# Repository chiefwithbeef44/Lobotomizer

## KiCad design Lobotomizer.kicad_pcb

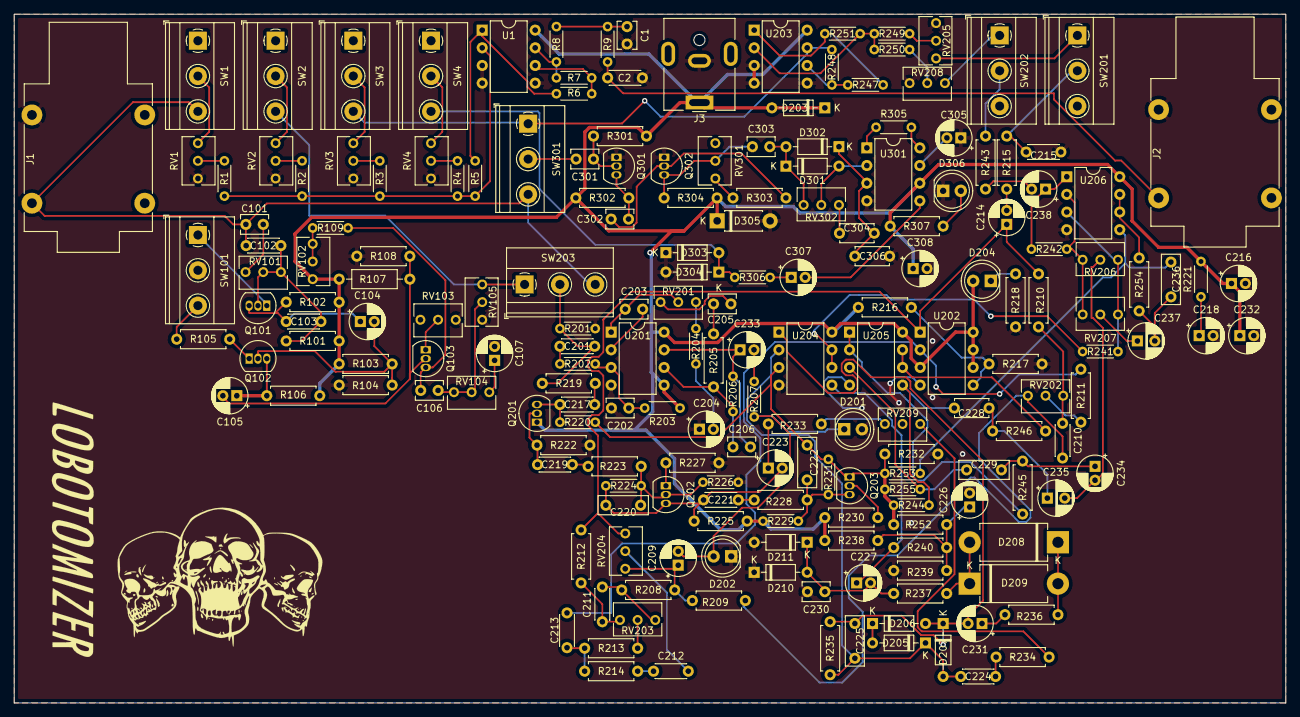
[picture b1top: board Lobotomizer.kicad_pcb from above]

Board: 2 copper layers, 182.9 x 99.1 mm, 198 parts (0 on the bottom side), 128 nets.

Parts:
C1, C202, C230: 1n; C_Disc_D3.8mm_W2.6mm_P2.50mm
C2: 680p; C_Disc_D4.3mm_W1.9mm_P5.00mm
C101, C106, C205, C301, C302, C303: 100n; C_Disc_D3.8mm_W2.6mm_P2.50mm
C102, C211, C213: 10n; C_Disc_D4.3mm_W1.9mm_P5.00mm
C103: 470p; C_Disc_D4.3mm_W1.9mm_P5.00mm
C104, C105, C305: 4.7u; CP_Radial_D5.0mm_P2.00mm
C107: 330n; CP_Radial_D5.0mm_P2.00mm
C201, C215: 22n; C_Disc_D4.3mm_W1.9mm_P5.00mm
C203, C206: 100p; C_Disc_D3.8mm_W2.6mm_P2.50mm
C204: 220n; CP_Radial_D5.0mm_P2.00mm
C209, C214, C233: 2.2u; CP_Radial_D5.0mm_P2.00mm
C210, C217, C219, C221, C224: 47n; C_Disc_D4.3mm_W1.9mm_P5.00mm
C212: 2.2n; C_Disc_D4.3mm_W1.9mm_P5.00mm
C216, C232, C307, C308: 100u; CP_Radial_D5.0mm_P2.00mm
C218, C226: 47u; CP_Radial_D5.0mm_P2.00mm
C220, C222, C225: 10p; C_Disc_D7.0mm_W2.5mm_P5.00mm
C223, C238: 10u; CP_Radial_D5.0mm_P2.00mm
C227, C231: 1u; CP_Radial_D5.0mm_P2.00mm
C228, C304: 6.8n; C_Disc_D4.7mm_W2.5mm_P5.00mm
C229: 4.7n; C_Disc_D7.0mm_W2.5mm_P5.00mm
C234: 0.1u; CP_Radial_D5.0mm_P2.00mm
C235: 0.15u; CP_Radial_D5.0mm_P2.50mm
C236: 68n; C_Disc_D7.0mm_W2.5mm_P5.00mm
C237: 1.5u; CP_Radial_D5.0mm_P2.50mm
C306: 220p; C_Disc_D4.7mm_W2.5mm_P5.00mm
D201, D202, D204, D306: LED; LED_D5.0mm
D203, D205, D206, D207, D210, D211: 4148; D_DO-35_SOD27_P7.62mm_Horizontal
D208, D209: SB2060; D_DO-201AD_P12.70mm_Horizontal
D301, D302, D303, D304: 5227; D_DO-35_SOD27_P7.62mm_Horizontal
D305: 4001; D_DO-41_SOD81_P7.62mm_Horizontal
J1: IN; Jack_6.35mm_Neutrik_NMJ4HFD2_Horizontal
J2: OUT; Jack_6.35mm_Neutrik_NMJ4HFD2_Horizontal
J3: POWER; BarrelJack_CUI_PJ-063AH_Horizontal
Q101, Q102: 5089; TO-92_Inline
Q103: 5308; TO-92_Inline
Q201: NTE457; TO-92_Inline
Q202: 2N3904; TO-92_Inline
Q203: KSA992; TO-92_Inline
Q301, Q302: MPSA05; TO-92_Inline
R1, R2, R3, R4, R5, R6, R7, R8, R9, R226, R229, R244, R247, R248, R249, R250, R251, R253, R255: 100K; R_Axial_DIN0204_L3.6mm_D1.6mm_P5.08mm_Horizontal
R101, R103, R108, R301: 910K; R_Axial_DIN0207_L6.3mm_D2.5mm_P7.62mm_Horizontal
R102, R106, R302, R304: 180K; R_Axial_DIN0207_L6.3mm_D2.5mm_P7.62mm_Horizontal
R104: 910; R_Axial_DIN0207_L6.3mm_D2.5mm_P7.62mm_Horizontal
R105, R205, R214, R219, R222, R225, R232, R236, R237, R238, R239, R243, R307: 10K; R_Axial_DIN0207_L6.3mm_D2.5mm_P7.62mm_Horizontal
R107: 4.7M; R_Axial_DIN0207_L6.3mm_D2.5mm_P10.16mm_Horizontal
R109: 750; R_Axial_DIN0204_L3.6mm_D1.6mm_P5.08mm_Horizontal
R201, R203, R206, R220: 1M; R_Axial_DIN0204_L3.6mm_D1.6mm_P5.08mm_Horizontal
R202, R204, R221, R305: 1K; R_Axial_DIN0204_L3.6mm_D1.6mm_P5.08mm_Horizontal
R207: 470; R_Axial_DIN0204_L3.6mm_D1.6mm_P5.08mm_Horizontal
R208, R212: 2.2K; R_Axial_DIN0207_L6.3mm_D2.5mm_P7.62mm_Horizontal
R209, R210, R215: 6.8K; R_Axial_DIN0207_L6.3mm_D2.5mm_P7.62mm_Horizontal
R211, R240, R252: 68K; R_Axial_DIN0207_L6.3mm_D2.5mm_P7.62mm_Horizontal
R213: 15K; R_Axial_DIN0207_L6.3mm_D2.5mm_P7.62mm_Horizontal
R216, R217, R223, R228: 22K; R_Axial_DIN0207_L6.3mm_D2.5mm_P7.62mm_Horizontal
R218, R303: 4.7K; R_Axial_DIN0207_L6.3mm_D2.5mm_P7.62mm_Horizontal
R224, R231: 470K; R_Axial_DIN0204_L3.6mm_D1.6mm_P5.08mm_Horizontal
R227: 22; R_Axial_DIN0207_L6.3mm_D2.5mm_P7.62mm_Horizontal
R230: 120; R_Axial_DIN0207_L6.3mm_D2.5mm_P7.62mm_Horizontal
R233: 150; R_Axial_DIN0207_L6.3mm_D2.5mm_P7.62mm_Horizontal
R234: 47K; R_Axial_DIN0207_L6.3mm_D2.5mm_P7.62mm_Horizontal
R235: 220K; R_Axial_DIN0207_L6.3mm_D2.5mm_P7.62mm_Horizontal
R241, R242: 3.3K; R_Axial_DIN0204_L3.6mm_D1.6mm_P5.08mm_Horizontal
R245, R246, R254: 330; R_Axial_DIN0207_L6.3mm_D2.5mm_P7.62mm_Horizontal
R306: 220; R_Axial_DIN0204_L3.6mm_D1.6mm_P5.08mm_Horizontal
RV1, RV2, RV3, RV4, RV101, RV105, RV201, RV204, RV205: 100K; Potentiometer_Bourns_3266Y_Vertical
RV102: 50K; Potentiometer_Bourns_3266Y_Vertical
RV103, RV104, RV206, RV207, RV208: 10K; Potentiometer_Bourns_3266Y_Vertical
RV202, RV203: 25K; Potentiometer_Bourns_3266Y_Vertical
RV209: 250K; Potentiometer_Bourns_3266Y_Vertical
RV301, RV302: 1M; Potentiometer_Bourns_3266Y_Vertical
SW1, SW2, SW3, SW4, SW201, SW202, SW203, SW301: SW_SPDT; TerminalBlock_Phoenix_MKDS-1,5-3-5.08_1x03_P5.08mm_Horizont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
SW101: SW_SPDT_MSM; TerminalBlock_Phoenix_MKDS-1,5-3-5.08_1x03_P5.08mm_Horizont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
U1, U202, U203: TL082; DIP-8_W7.62mm
U201, U204, U205, U206: LM833; DIP-8_W7.62mm
U301: LM386; DIP-8_W7.62mm

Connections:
4.5V: C222.1, Q203.1, R220.1, R231.1, R232.1, R244.2, R252.2, R253.2, R255.2, U204.3
FUZZ_OUT: RV105.3, SW2.3, SW203.1
GND: C1.2, C2.2, C107.2, C202.2, C204.1, C215.2, C216.2, C218.2, C226.2, C230.2, C232.2, C305.1, C306.2, C308.2, D201.2, D202.1, D210.1, D211.2, D303.1, D304.2, D305.2, D306.1, J1.S, J2.S, J3.2, Q301.1, Q302.1, R104.2, R108.2, R201.2, R217.2, R218.1, R222.2, R226.2, R227.2, R232.2, R239.2, RV1.3, RV2.3, RV3.3, RV4.3, RV103.1, RV105.1, RV205.3, RV208.3, RV209.2, SW101.2, U1.3, U1.4, U1.5, U201.4, U202.4, U203.3, U203.4, U203.5, U204.4, U205.4, U206.4, U301.4
MEGAFUCKER_OUT: R248.1, SW3.3, SW301.1, U203.7
unnamed: C1.1, R8.1, R9.2
unnamed: C2.1, J2.T, R9.1
unnamed: C101.1, RV101.3
unnamed: C102.1, C103.2, Q101.2, R101.2, RV101.1, RV101.2
unnamed: C103.1, C104.1, Q101.3, R102.2
unnamed: C104.2, Q102.2, R103.2, R104.1
unnamed: C105.1, Q102.3, R106.2
unnamed: C105.2, Q103.2, R107.2, R108.1
unnamed: C106.1, RV104.2, RV104.3, RV105.2
unnamed: C106.2, Q103.3, R109.2
unnamed: C107.1, RV104.1
unnamed: C201.1, R202.2
unnamed: C201.2, R201.1, R219.2, SW203.2
unnamed: C202.1, R202.1, R203.2, U201.3
unnamed: C203.1, RV201.2, U201.1
unnamed: C203.2, U201.2
unnamed: C204.2, R204.2
unnamed: C205.1, R205.2
unnamed: C205.2, RV201.3
unnamed: C206.1, R205.1, R206.1, U201.6
unnamed: C206.2, C233.1, R206.2, U201.7
unnamed: C209.1, R208.2, R209.2, RV204.3
unnamed: C209.2, D201.1, D202.2, R207.1
unnamed: C210.1, R210.2, RV202.1
unnamed: C210.2, R209.1, RV202.3
unnamed: C211.1, R212.2, RV203.1
unnamed: C211.2, R208.1, RV203.3
unnamed: C212.1, R214.2
unnamed: C212.2, RV204.2
unnamed: C213.1, R211.1, U202.2
unnamed: C213.2, R213.1, R214.1
unnamed: C214.1, R210.1, R212.1, RV204.1, U202.1
unnamed: C214.2, R215.2
unnamed: C215.1, R215.1, SW201.2
unnamed: C217.1, Q201.3, R220.2
unnamed: C217.2, R219.1
unnamed: C218.1, R221.1
unnamed: C219.1, R223.2
unnamed: C219.2, Q201.2, R222.1
unnamed: C220.1, C221.2, C223.2, Q202.3, R224.1, R225.2
unnamed: C220.2, Q202.2, R223.1, R224.2, R226.1
unnamed: C221.1, R228.2
unnamed: C222.2, Q203.3, R228.1, R229.2, R231.2
unnamed: C223.1, R233.2
unnamed: C224.1, C225.2, D205.1, D207.2, R235.2, U204.2
unnamed: C224.2, R234.1
unnamed: C225.1, C231.2, D206.2, D207.1, R235.1, U204.1
unnamed: C226.1, R238.2, R239.1, R240.1, R252.1
unnamed: C227.1, R240.2, U204.5
unnamed: C227.2, C230.1, D210.2, D211.1, R237.1
unnamed: C228.1, C235.1, R246.1
unnamed: C228.2, R244.1, U205.5
unnamed: C229.1, C234.1, R245.1
unnamed: C229.2, R255.1, U205.3
unnamed: C231.1, R236.2
unnamed: C233.2, R207.2
unnamed: C234.2, C235.2, RV206.2
unnamed: C236.1, C237.2, R254.1
unnamed: C236.2, R253.1, U206.5
unnamed: C237.1, RV207.2
unnamed: C238.1, R242.1, U206.1
unnamed: C238.2, R243.2
unnamed: C301.1, Q301.2, R301.2
unnamed: C301.2, SW301.2
unnamed: C302.1, Q302.2, R303.1
unnamed: C302.2, Q301.3, R302.2
unnamed: C303.1, Q302.3, R304.2, RV301.2
unnamed: C303.2, D301.1, D302.2, RV302.1
unnamed: C304.1, C306.1, D302.1, U301.3
unnamed: C304.2, RV302.3
unnamed: C305.2, U301.7
unnamed: C307.1, R306.2
unnamed: C307.2, U301.5
unnamed: D204.1, R218.2
unnamed: D205.2, D206.1
unnamed: D208.1, D209.2, R236.1
unnamed: D208.2, D209.1, R237.2
unnamed: D301.2, RV302.2, U301.2
unnamed: D306.2, R307.1
unnamed: Q101.1, SW101.1
unnamed: Q102.1, R105.2
unnamed: Q103.1, RV103.2
unnamed: Q202.1, R227.1
unnamed: Q203.2, R230.2
unnamed: R1.1, R2.1, R3.1, R4.1, R5.2, U1.2
unnamed: R1.2, RV1.2
unnamed: R2.2, RV2.2
unnamed: R3.2, RV3.2
unnamed: R4.2, RV4.2
unnamed: R5.1, R6.2, U1.1
unnamed: R6.1, R7.2, U1.6
unnamed: R7.1, R8.2, U1.7
unnamed: R105.1, SW101.3
unnamed: R109.1, RV102.1, RV102.2
unnamed: R204.1, RV201.1
unnamed: R211.2, RV202.2
unnamed: R213.2, RV203.2
unnamed: R216.2, R217.1, U202.5
unnamed: R233.1, RV209.3
unnamed: R234.2, RV209.1
unnamed: R241.1, RV206.3, RV207.3, U206.3
unnamed: R241.2, U204.6, U204.7
unnamed: R242.2, RV206.1, RV207.1, U206.2
unnamed: R243.1, SW202.2
unnamed: R245.2, U205.1, U205.2
unnamed: R246.2, U205.6, U205.7
unnamed: R247.1, R248.2, U203.6
unnamed: R247.2, R251.1, U203.1
unnamed: R249.1, R250.1, R251.2, U203.2
unnamed: R249.2, RV205.2
unnamed: R250.2, RV208.2
unnamed: R254.2, U206.6, U206.7
unnamed: R303.2, RV301.1
unnamed: R305.1, U301.1
unnamed: R305.2, U301.8
unnamed: RV1.1, SW1.2
unnamed: RV2.1, SW2.2
unnamed: RV3.1, SW3.2
unnamed: RV4.1, SW4.2
unnamed: RV205.1, SW201.1
unnamed: RV208.1, SW202.1
SAW_OUT: D303.2, D304.1, R306.1, SW4.3
SIGNAL_IN: C101.2, C102.2, J1.T, SW1.3, SW203.3, SW301.3
VCLEAN: C216.1, C232.1, C308.1, D203.1, D203.2, D204.2, D305.1, J3.1, Q201.1, R101.1, R102.1, R103.1, R106.1, R107.1, R203.1, R216.1, R221.2, R225.1, R229.1, R230.1, R238.1, R301.1, R302.1, R304.1, R307.2, RV102.3, U1.8, U201.5, U201.8, U202.3, U202.6, U202.7, U202.8, U203.8, U204.8, U205.8, U206.8, U301.6

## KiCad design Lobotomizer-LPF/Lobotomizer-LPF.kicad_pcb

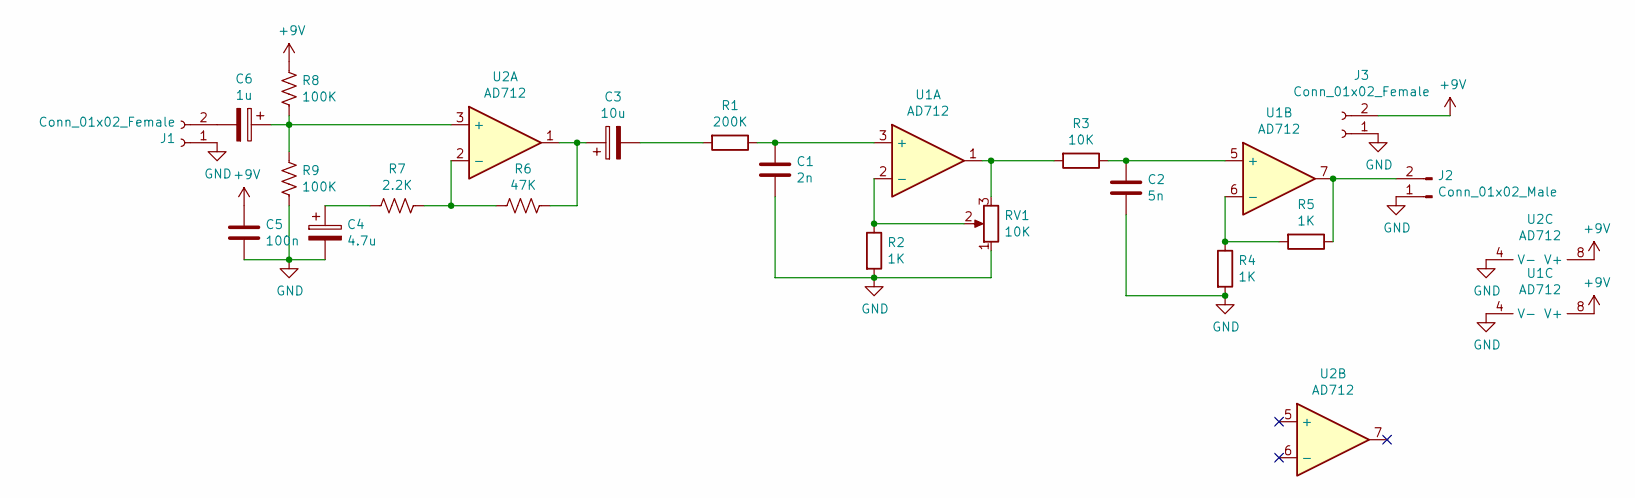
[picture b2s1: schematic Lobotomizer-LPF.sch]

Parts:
C1: 2n; C_Disc_D4.7mm_W2.5mm_P5.00mm
C2: 5n; C_Disc_D4.7mm_W2.5mm_P5.00mm
C3: 10u; CP_Radial_D5.0mm_P2.50mm
C4: 4.7u; CP_Radial_D5.0mm_P2.50mm
C5: 100n; C_Disc_D5.0mm_W2.5mm_P5.00mm
C6: 1u; CP_Radial_D5.0mm_P2.50mm
J1, J3: Conn_01x02_Female; PinHeader_1x02_P2.54mm_Vertical
J2: Conn_01x02_Male; PinHeader_1x02_P2.54mm_Vertical
R1: 200K; R_Axial_DIN0207_L6.3mm_D2.5mm_P10.16mm_Horizontal
R2, R4, R5: 1K; R_Axial_DIN0207_L6.3mm_D2.5mm_P7.62mm_Horizontal
R3: 10K; R_Axial_DIN0207_L6.3mm_D2.5mm_P7.62mm_Horizontal
R6: 47K; R_Axial_DIN0614_L14.3mm_D5.7mm_P25.40mm_Horizontal
R7: 2.2K; R_Axial_DIN0207_L6.3mm_D2.5mm_P7.62mm_Horizontal
R8, R9: 100K; R_Axial_DIN0207_L6.3mm_D2.5mm_P10.16mm_Horizontal
RV1: 10K; Potentiometer_Bourns_3266Y_Vertical
U1, U2: AD712; DIP-8_W7.62mm_LongPads

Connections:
+9V: C5.1, J3.2, R8.1, U1.8 (V+), U2.8 (V+)
GND: C1.2, C2.2, C4.2, C5.2, J1.1, J2.1, J3.1, R2.2, R4.2, R9.2, RV1.1, U1.4 (V-), U2.4 (V-)
unnamed: C1.1, R1.1, U1.3 (+)
unnamed: C2.1, R3.1, U1.5 (+)
unnamed: C3.1, R6.1, U2.1
unnamed: C3.2, R1.2
unnamed: C4.1, R7.2
unnamed: C6.1, R8.2, R9.1, U2.3 (+)
unnamed: C6.2, J1.2
unnamed: J2.2, R5.1, U1.7
unnamed: R2.1, RV1.2, U1.2 (-)
unnamed: R3.2, RV1.3, U1.1
unnamed: R4.1, R5.2, U1.6 (-)
unnamed: R6.2, R7.1, U2.2 (-)

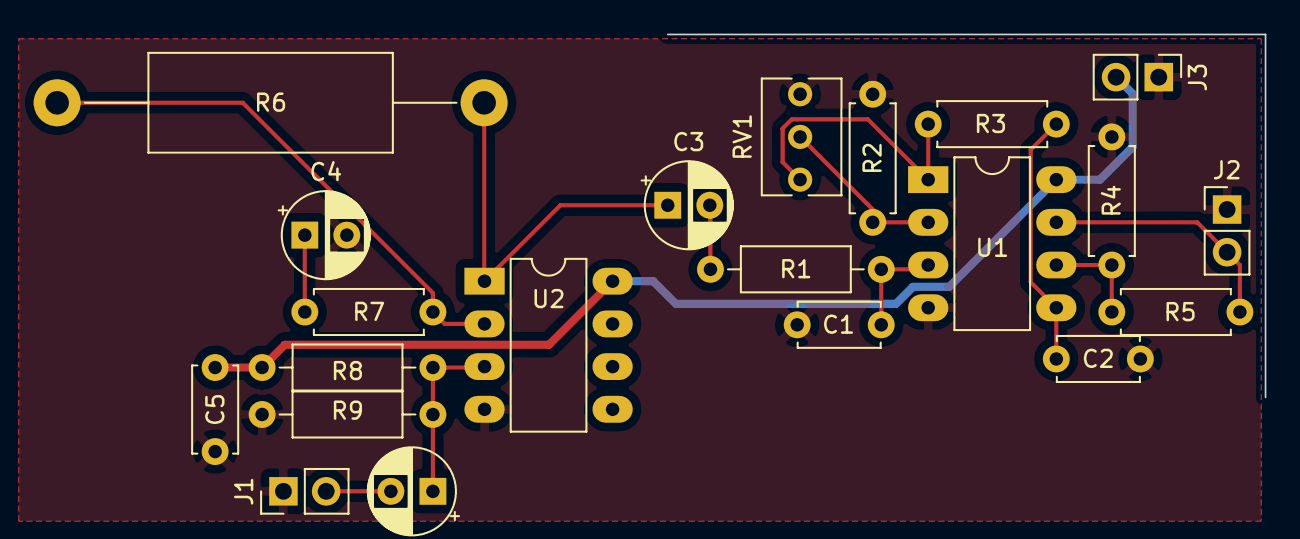
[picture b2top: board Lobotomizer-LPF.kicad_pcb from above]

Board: 2 copper layers, 21 parts (0 on the bottom side), 14 nets.

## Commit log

2022-01-02 finished pcb layout
2022-01-03 finalized v1 design
2022-01-03 add bom
2022-01-04 fixed major error
    U207:7 now connected to VCLEAN.
2022-01-04 changed to pos tip, gnd sleeve jack.
2022-01-04 updated gbrs
2022-01-13 dimensions
2022-02-07 lobotomizer v2 update
    so much changed i cant note it all here
2022-02-07 updated gerbers
2022-02-18 v2 board gerbers
